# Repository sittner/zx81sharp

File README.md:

# zx81sharp

This is essentially a redraw of Mahjongg's great [ZX81plus38](https://github.com/mahjongg2/ZX81plus38) project.
I've done it to be able to fix and modify some issues:

* fixed pinout of tape connectors CO2/CO3
* fixed rotation/position of keyboard connector J3
* fixed CPU clock phase
* fixed position of connectors and mounting holes
* replaced USB power connector with  2.1/2.5 mm power plug
* simplified memory address decoder to allow full usage of RAM/ROM memory
* fixed video output sync latch to avoid ghost lines

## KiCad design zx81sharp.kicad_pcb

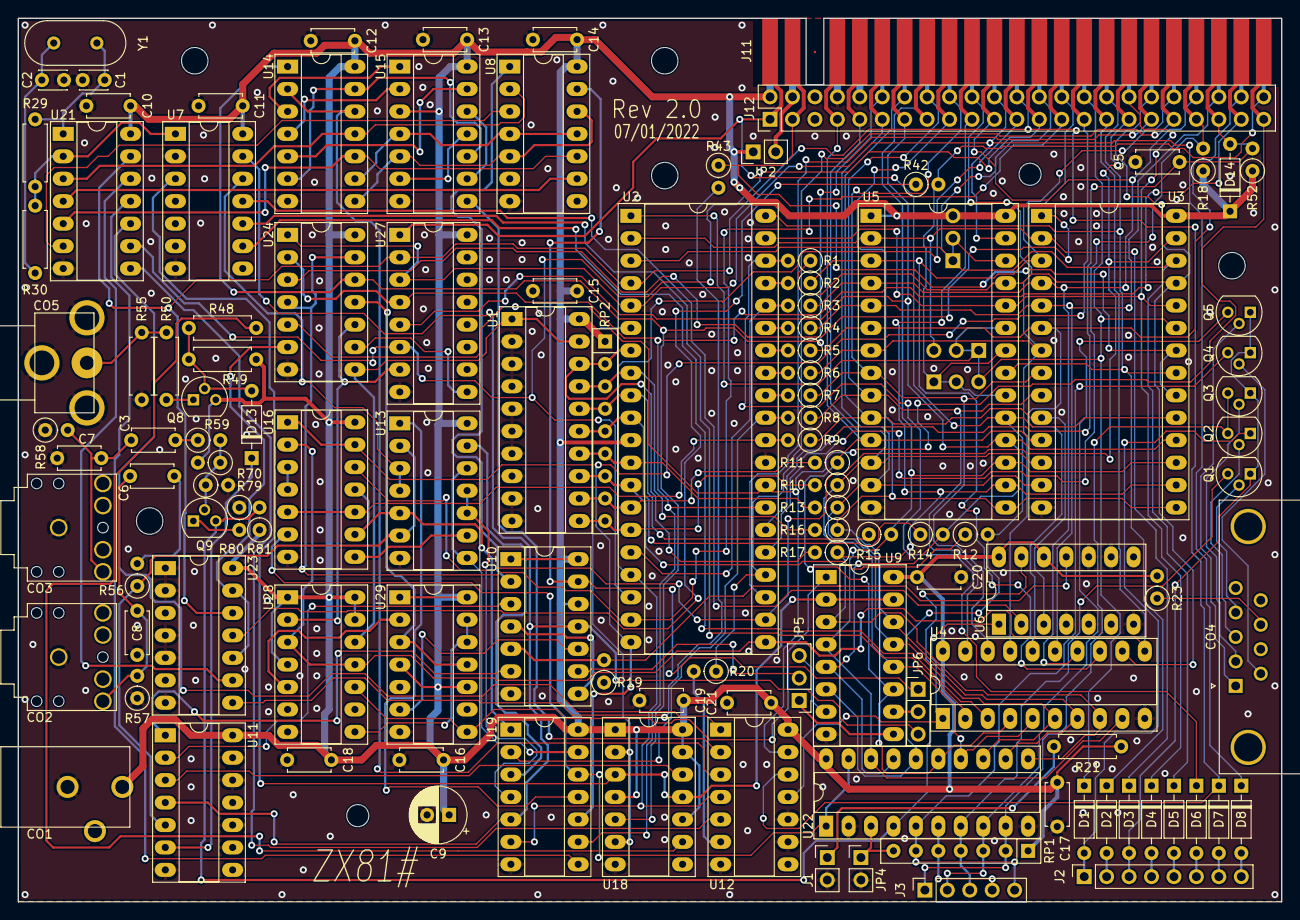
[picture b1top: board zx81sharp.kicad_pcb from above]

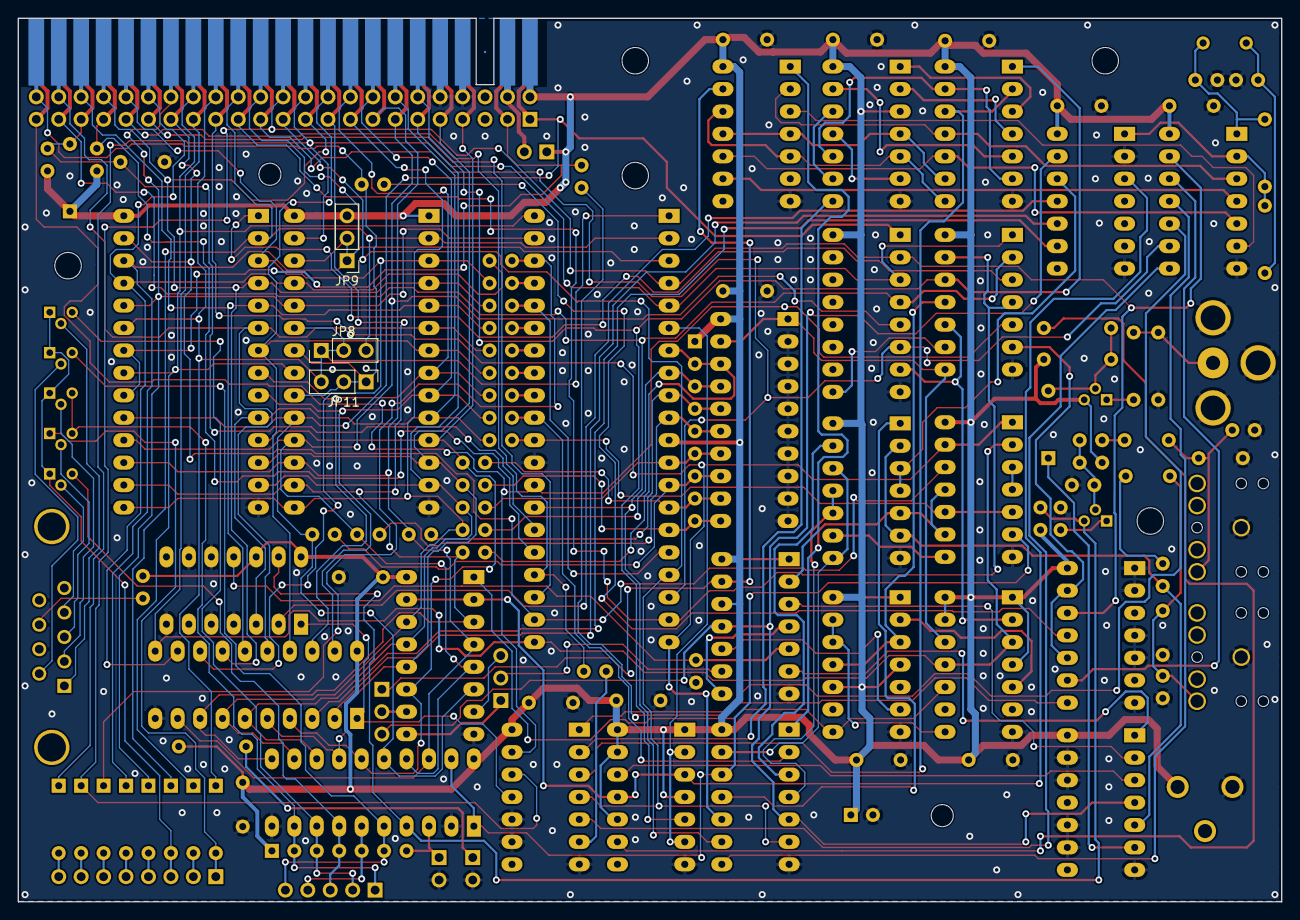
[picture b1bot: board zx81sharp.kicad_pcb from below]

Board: 2 copper layers, 143.0 x 100.0 mm, 128 parts (3 on the bottom side), 154 nets.

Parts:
C1, C2: 4p7; C_Disc_D3.0mm_W2.0mm_P2.50mm
C3: 4n7; C_Disc_D4.7mm_W2.5mm_P5.00mm
C5: 1u; C_Disc_D4.7mm_W2.5mm_P5.00mm
C6, C10, C11, C12, C13, C14, C15, C16, C17, C18, C19, C20, C21: 100n; C_Disc_D4.7mm_W2.5mm_P5.00mm
C7, C8: 47p; C_Disc_D4.7mm_W2.5mm_P5.00mm
C9: 100u; CP_Radial_D6.3mm_P2.50mm
CO1: Power in; Jack_Barrel_CLIFF_FCR681465P
CO2: Tape out; Jack_3.5mm_MULTICOMP_SPC21348
CO3: Tape in; Jack_3.5mm_MULTICOMP_SPC21348
CO4: Joystick; DSUB-9_Male_Horizontal_P2.77x2.84mm_EdgePinOffset7.70mm_Hou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
CO5: Video out; RCA_CON_CLIFF_FC68391
D1, D2, D3, D4, D5, D6, D7, D8, D14: 1N4148; D_DO-35_SOD27_P7.62mm_Horizontal
D13: BAT43; D_DO-35_SOD27_P7.62mm_Horizontal
H1, H2, H3, H4, H7: MountingHole 3.0mm; MountingHole_3mm
H5, H6: MountingHole 2.5mm; MountingHole_2.5mm
J1: LED on; PinHeader_1x02_P2.54mm_Vertical
J2: KB2; PinSocket_1x08_P2.54mm_Vertical
J3: KB1; PinSocket_1x05_P2.54mm_Vertical
J11: Expansion Header; ZX81_EXP
J12: Expansion Header; PinHeader_2x23_P2.54mm_Vertical
JP2: Jumper_2_Open; PinHeader_1x02_P2.54mm_Vertical
JP4: 60Hz; PinHeader_1x02_P2.54mm_Vertical
JP5: Invert; PinHeader_1x03_P2.54mm_Vertical
JP6: Border; PinHeader_1x03_P2.54mm_Vertical
JP8, JP9, JP11: Jumper_3_Bridged12; PinHeader_1x03_P2.54mm_Vertical
Q1, Q2, Q3, Q4, Q5, Q8, Q9: 2N3904; TO-92
R1, R2, R3, R4, R5, R6, R7, R8, R9, R10, R11, R12, R13, R14, R15, R16, R17, R58: 1k; R_Axial_DIN0207_L6.3mm_D2.5mm_P2.54mm_Vertical
R18, R19, R23, R52, R59, R81: 10k; R_Axial_DIN0207_L6.3mm_D2.5mm_P2.54mm_Vertical
R20, R42, R43: 680R; R_Axial_DIN0207_L6.3mm_D2.5mm_P2.54mm_Vertical
R21: 330R; R_Axial_DIN0207_L6.3mm_D2.5mm_P7.62mm_Horizontal
R29: 2M2; R_Axial_DIN0207_L6.3mm_D2.5mm_P7.62mm_Horizontal
R30, R49: 1k; R_Axial_DIN0207_L6.3mm_D2.5mm_P7.62mm_Horizontal
R48: 470R; R_Axial_DIN0207_L6.3mm_D2.5mm_P7.62mm_Horizontal
R50, R55: 100R; R_Axial_DIN0207_L6.3mm_D2.5mm_P7.62mm_Horizontal
R56: 47k; R_Axial_DIN0207_L6.3mm_D2.5mm_P2.54mm_Vertical
R57: 2k2; R_Axial_DIN0207_L6.3mm_D2.5mm_P2.54mm_Vertical
R70: 220k; R_Axial_DIN0207_L6.3mm_D2.5mm_P2.54mm_Vertical
R79: 82k; R_Axial_DIN0207_L6.3mm_D2.5mm_P2.54mm_Vertical
R80: 220R; R_Axial_DIN0207_L6.3mm_D2.5mm_P2.54mm_Vertical
RP1: 10k; R_Array_SIP7
RP2: 22k; R_Array_SIP9
U1, U22: 74HC541; DIP-20_W7.62mm_Socket_LongPads
U2: Z80CPU; DIP-40_W15.24mm_Socket_LongPads
U3: KM62256CLP; DIP-28_W15.24mm_Socket_LongPads
U4: 74HC574; DIP-20_W7.62mm_Socket_LongPads
U5: 27C256; DIP-28_W15.24mm_Socket_LongPads
U6: 74HC125; DIP-14_W7.62mm_Socket_LongPads
U7, U14: 74HC393; DIP-14_W7.62mm_Socket_LongPads
U8: 74HC4002; DIP-14_W7.62mm_Socket_LongPads
U9: 74HC165; DIP-16_W7.62mm_Socket_LongPads
U10: 74HC86; DIP-14_W7.62mm_Socket_LongPads
U11, U24: 74HC08; DIP-14_W7.62mm_Socket_LongPads
U12, U16, U19, U23: 74HC32; DIP-14_W7.62mm_Socket_LongPads
U13: 74HC00; DIP-14_W7.62mm_Socket_LongPads
U15: 74HC11; DIP-14_W7.62mm_Socket_LongPads
U18, U28, U29: 74HC74; DIP-14_W7.62mm_Socket_LongPads
U21: 74HC14; DIP-14_W7.62mm_Socket_LongPads
U27: 74HC138; DIP-16_W7.62mm_Socket_LongPads
Y1: 13MHz; Crystal_HC49-4H_Vertical

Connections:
+5V: C9.1, C10.1, C11.1, C12.1, C13.1, C14.1, C15.1, C16.1, C17.1, C18.1, C19.1, C20.1, C21.1, CO1.1, D14.1, J11.1b, J12.2, JP2.1, JP9.3, Q8.3, R18.1, R21.1, R23.2, R49.1, R52.1, R70.2, R81.1, RP1.1, RP2.1, U1.20, U2.11, U3.28, U4.20, U5.1, U5.28, U6.12, U6.14, U7.14, U8.14, U9.16, U10.1, U10.12, U10.14, U11.14, U12.14, U13.14, U14.14, U15.3, U15.14, U16.14, U18.1, U18.4, U18.10, U18.13, U18.14, U19.14, U21.14, U22.20, U23.14, U24.14, U27.16, U28.1, U28.4, U28.13, U28.14, U29.1, U29.4, U29.10, U29.14
+9V: J11.2b, J12.4, JP2.2
/3.25M: J11.6b, J12.12, U14.1, U18.5, U24.12
/6.5M: U7.3, U9.2, U9.15, U18.3, U18.11
/A0: R9.2, U2.30, U16.5, U16.10
/A0': J11.7b, J12.14, R9.1, U3.10, U5.10, U6.3
/A1: R8.2, U2.31, U19.2
/A1': J11.8b, J12.16, R8.1, U3.9, U4.19, U5.9
/A2: R7.2, U2.32
/A2': J11.9b, J12.18, R7.1, U3.8, U4.18, U5.8
/A3: R6.2, U2.33
/A3': J11.10b, J12.20, R6.1, U3.7, U4.17, U5.7
/A4: R5.2, U2.34
/A4': J11.22b, J12.44, R5.1, U3.6, U4.16, U5.6
/A5: R4.2, U2.35
/A5': J11.21b, J12.42, R4.1, U3.5, U4.15, U5.5
/A6: R3.2, U2.16, U2.36
/A6': J11.11a, J11.20b, J12.21, J12.40, R3.1, U3.4, U4.14, U5.4
/A7: R2.2, U2.37
/A7': J11.19b, J12.38, R2.1, U3.3, U4.13, U5.3
/A8: D6.1, R1.2, U2.38
/A8': J11.18b, J12.36, R1.1, U3.25, U4.12, U5.25
/A9: D4.1, J11.17b, J12.34, U2.39, U3.24, U5.24
/A10: D2.1, J11.16b, J12.32, U2.40, U3.21, U5.21
/A11: D1.1, J11.15b, J12.30, JP8.1, JP8.2, JP11.3, U2.1, U3.23, U5.23
/A12: D3.1, J11.14b, J12.28, JP8.3, U2.2, U3.2, U5.2
/A13: D5.1, J11.13b, J12.26, JP9.1, JP9.2, U2.3, U3.26, U5.26
/A14: D7.1, J11.12b, J12.24, U2.4, U12.12, U21.13, U23.12, U27.2
/A14_RAM: U3.1, U24.3
/A15: D8.1, J11.11b, J12.22, U2.5, U5.27, U24.1, U27.3
/CAS_IN: R19.2, U6.11, U10.5
/D0: R11.2, RP2.8, U1.12, U2.14
/D0': J11.4a, J12.7, R11.1, U3.11, U4.4, U5.11, U9.11, U22.15
/D1: R10.2, RP2.9, U1.11, U2.15
/D1': J11.5a, J12.9, R10.1, U3.12, U4.5, U5.12, U9.12, U22.14
/D2: R13.2, RP2.6, U1.14, U2.12
/D2': J11.6a, J12.11, R13.1, U3.13, U4.6, U5.13, U9.13, U22.13
/D3: R16.2, RP2.3, U1.17, U2.8
/D3': J11.9a, J12.17, R16.1, U3.15, U4.7, U5.15, U9.14, U22.12
/D4: R17.2, RP2.2, U1.18, U2.7
/D4': J11.10a, J12.19, R17.1, U3.16, U4.8, U5.16, U9.3, U22.11
/D5: R15.1, RP2.4, U1.16, U2.9
/D5': J11.8a, J12.15, R15.2, U3.17, U4.9, U5.17, U9.4, U22.18
/D6: R14.1, RP2.5, U1.15, U2.10
/D6': J11.7a, J12.13, R14.2, U3.18, U5.18, U9.5, U22.17, U27.5
/D7: R12.1, RP2.7, U1.13, U2.13
/D7': J11.1a, J12.1, R12.2, U3.19, U5.19, U9.6, U22.16, U27.1
/DOWN: CO4.2, Q3.2
/END: U12.3, U14.2, U14.12
/FRIRE: CO4.6, Q4.2
/HSYNC: JP6.1, U8.13, U10.13
/INVERT: U10.10, U29.6
/KBA11: D1.2, J2.1, Q2.1
/KBA12: D3.2, J2.3, Q1.1, Q3.1, Q4.1, Q5.1
/KBD0: J3.5, Q4.3, RP1.6, U22.5
/KBD1: J3.4, RP1.5, U22.6
/KBD2: J3.3, Q1.3, RP1.4, U22.7
/KBD3: J3.2, Q5.3, RP1.3, U22.8
/KBD4: J3.1, Q2.3, Q3.3, RP1.2, U22.9
/LEFT: CO4.3, Q2.2
/PIXEL: JP5.2, U10.9
/RIGHT: CO4.4, Q1.2
/ROW0: U6.2, U7.11
/ROW1: U4.2, U7.10
/ROW2: U4.3, U7.9
/UP: CO4.1, Q5.2
/VSYNC: U7.12, U13.3, U13.4
/n3.25M: U2.6, U18.2, U18.6
/nBUSACK: J11.18a, J12.35, U2.23
/nBUSRQ: J11.20a, J12.39, R18.2, U2.25
/nCAS_IN: Q9.3, R81.2, U6.13, U22.4
/nHALT: J11.13a, J12.25, U2.18, U21.9, U27.6
/nHSYNC: JP6.3, U7.13, U10.11, U11.4, U19.5
/nIN_FE: U16.6, U19.12, U22.1, U22.19
/nIORQ: J11.15a, J12.29, U2.20, U16.1, U16.13, U19.10
/nLD: U9.1, U28.10, U29.8
/nM1: J11.22a, J12.43, U2.27, U19.9, U24.2, U27.4
/nMREQ: J11.14a, J12.27, U2.19, U24.4, U24.13
/nNMI: J11.12a, J12.23, U2.17, U12.4, U19.6
/nNOP: U1.1, U1.19, U24.8, U28.12
/nOut: U13.5, U16.9, U16.11, U19.1
/nPORCH: U10.3, U11.2
/nRAMCS: J11.2a, J12.3, R43.1, U3.20, U3.22
/nRD: J11.16a, J12.31, U2.21, U4.11, U16.2, U28.3, U28.11
/nRESET: C5.1, D14.2, J11.21a, J12.41, R52.2, U2.26
/nRFSH: J11.23a, J12.45, U2.28, U12.13, U24.5
/nROMCS: J11.23b, J12.46, JP11.1, JP11.2, R42.2, U5.20, U5.22
/nVSYNC: R56.1, U11.5, U13.2, U13.6
/nWAIT: J11.19a, J12.37, R20.1, U2.24
/nWR: J11.17a, J12.33, U2.22, U3.27, U16.12
GND: C1.2, C2.2, C5.2, C7.2, C8.2, C9.2, C10.2, C11.2, C12.2, C13.2, C14.2, C15.2, C16.2, C17.2, C18.2, C19.2, C20.2, C21.2, CO1.2, CO2.G, CO3.G, CO5.2, J1.2, J11.4b, J11.5b, J12.8, J12.10, JP4.2, R19.1, R55.2, R57.1, R58.1, R79.2, R80.1, U1.2, U1.3, U1.4, U1.5, U1.6, U1.7, U1.8, U1.9, U1.10, U2.29, U3.14, U4.10, U5.14, U6.4, U6.5, U6.7, U6.9, U6.10, U7.2, U7.7, U8.7, U9.8, U10.7, U11.7, U11.9, U11.10, U11.12, U11.13, U12.7, U12.9, U12.10, U13.7, U14.7, U15.7, U16.7, U18.7, U19.7, U21.7, U22.2, U22.10, U23.1, U23.2, U23.4, U23.5, U23.7, U24.7, U27.8, U28.7, U29.7
unnamed: C1.1, R29.2, U21.1, Y1.1
unnamed: C2.1, R30.2, Y1.2
unnamed: C3.1, R59.1
unnamed: C3.2, C7.1, CO3.T, R58.2
unnamed: C6.1, R56.2
unnamed: C6.2, C8.1, CO2.T, R57.2
unnamed: CO4.8, R23.1
unnamed: CO5.1, R50.2, R55.1
unnamed: D2.2, J2.2
unnamed: D4.2, J2.4
unnamed: D5.2, J2.5
unnamed: D6.2, J2.6
unnamed: D7.2, J2.7
unnamed: D8.2, J2.8
unnamed: D13.1, U11.6
unnamed: D13.2, Q8.2, R48.2, R49.2
unnamed: J1.1, R21.2
unnamed: JP4.1, RP1.7, U22.3
unnamed: JP5.1, U9.9
unnamed: JP5.3, U9.7
unnamed: JP6.2, U9.10
unnamed: Q8.1, R50.1
unnamed: Q9.1, R80.2
unnamed: Q9.2, R59.2, R70.1, R79.1
unnamed: R20.2, U12.6
unnamed: R29.1, R30.1, U7.1, U21.2
unnamed: R42.1, U23.11
unnamed: R43.2, U23.8
unnamed: R48.1, U18.9
unnamed: U8.1, U10.2
unnamed: U10.4, U10.8
unnamed: U10.6, U11.1
unnamed: U11.3, U18.12
unnamed: U12.1, U21.10
unnamed: U12.2, U15.8
unnamed: U12.5, U21.8
unnamed: U4.1, U6.1, U12.11
unnamed: U13.1, U19.11
unnamed: U13.9, U16.8
unnamed: U13.10, U13.11, U19.4
unnamed: U13.8, U13.12, U19.13
unnamed: U13.13, U19.3
unnamed: U14.3, U15.1
unnamed: U14.4, U15.2
unnamed: U14.5, U15.13
unnamed: U8.5, U8.12, U14.8, U15.5
unnamed: U8.4, U8.11, U14.9, U15.4
unnamed: U8.10, U14.10, U21.5
unnamed: U8.2, U14.11, U21.3
unnamed: U14.6, U14.13, U15.10
unnamed: U15.6, U15.11
unnamed: U15.9, U15.12
unnamed: U16.3, U16.4
unnamed: U19.8, U21.11
unnamed: U8.9, U21.4
unnamed: U8.3, U21.6
unnamed: U21.12, U23.9
unnamed: U23.10, U23.13, U24.6
unnamed: U24.9, U27.9
unnamed: U24.10, U27.7, U28.2
unnamed: U24.11, U29.3, U29.11
unnamed: U28.5, U29.2
unnamed: U28.8, U29.12, U29.13

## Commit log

2022-01-05 added gitignore file
2022-01-05 fixed mounting hole positions
2022-01-05 fixed keyboard connector
2022-01-07 fixed CPU clock, memory decoder and video output latch
2022-01-08 finished rev 2.0
2022-01-09 renamed project to zx81sharp
2022-01-11 cosmetic fixes
2022-01-27 added README.md
2022-01-27 added initial BOM
2022-01-27 added missed fix to README.md
